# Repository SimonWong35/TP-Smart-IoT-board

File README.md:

# TP-Smart-IoT-board

## Schematic

## Layout (71mm x 60mm)

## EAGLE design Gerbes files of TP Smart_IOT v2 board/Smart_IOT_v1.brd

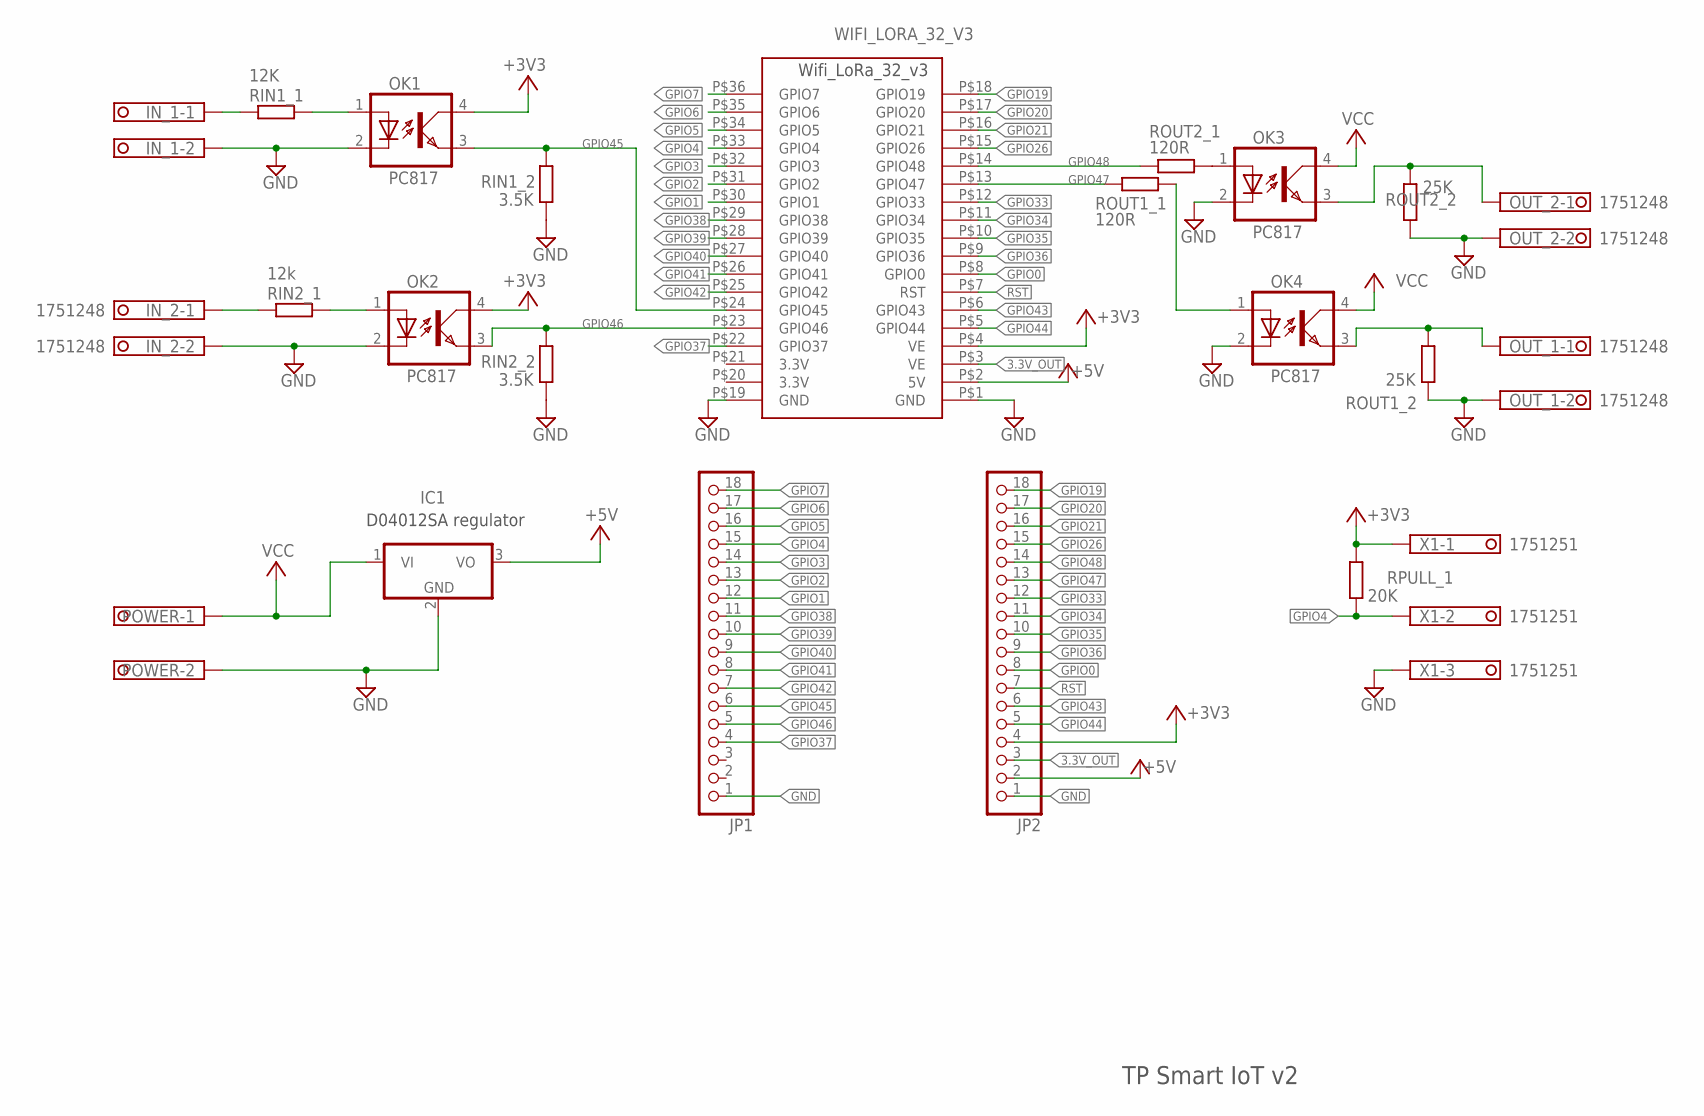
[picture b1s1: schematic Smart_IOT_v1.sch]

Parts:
IC1: 7805TV; TO220V
IN_1, IN_2: 1751248
JP1, JP2: PINHD-1X18; 1X18
OK1, OK2, OK3, OK4: PC817; DIL04
OUT_1, OUT_2: 1751248
POWER: 1751248
RIN1_1: 12K; M1206
RIN1_2, RIN2_2: 3.5K; M1206
RIN2_1: 12k; M1206
ROUT1_1, ROUT2_1: 120R; M1206
ROUT1_2, ROUT2_2: 25K; M1206
RPULL_1: 20K; M1206
WIFI_LORA_32_V3: WIFI_LORA_32_V3
X1: 1751251

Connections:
3.3V_OUT: JP2.3, WIFI_LORA_32_V3.P$3 (VE)
+3V3: JP2.4, OK1.4 (COL), OK2.4 (COL), RPULL_1.2, WIFI_LORA_32_V3.P$4 (VE), X1.1
+5V: IC1.3 (VO), JP2.2, WIFI_LORA_32_V3.P$2 (5V)
GND: IC1.2 (GND), IN_1.2, IN_2.2, JP1.1, JP2.1, OK1.2 (C), OK2.2 (C), OK3.2 (C), OK4.2 (C), OUT_1.2, OUT_2.2, POWER.2, RIN1_2.1, RIN2_2.1, ROUT1_2.1, ROUT2_2.2, WIFI_LORA_32_V3.P$1 (GND), WIFI_LORA_32_V3.P$19 (GND), X1.3
GPIO0: JP2.8, WIFI_LORA_32_V3.P$8 (GPIO0)
GPIO1: JP1.12, WIFI_LORA_32_V3.P$30 (GPIO1)
GPIO2: JP1.13, WIFI_LORA_32_V3.P$31 (GPIO2)
GPIO3: JP1.14, WIFI_LORA_32_V3.P$32 (GPIO3)
GPIO4: JP1.15, RPULL_1.1, WIFI_LORA_32_V3.P$33 (GPIO4), X1.2
GPIO5: JP1.16, WIFI_LORA_32_V3.P$34 (GPIO5)
GPIO6: JP1.17, WIFI_LORA_32_V3.P$35 (GPIO6)
GPIO7: JP1.18, WIFI_LORA_32_V3.P$36 (GPIO7)
GPIO19: JP2.18, WIFI_LORA_32_V3.P$18 (GPIO19)
GPIO20: JP2.17, WIFI_LORA_32_V3.P$17 (GPIO20)
GPIO21: JP2.16, WIFI_LORA_32_V3.P$16 (GPIO21)
GPIO26: JP2.15, WIFI_LORA_32_V3.P$15 (GPIO26)
GPIO33: JP2.12, WIFI_LORA_32_V3.P$12 (GPIO33)
GPIO34: JP2.11, WIFI_LORA_32_V3.P$11 (GPIO34)
GPIO35: JP2.10, WIFI_LORA_32_V3.P$10 (GPIO35)
GPIO36: JP2.9, WIFI_LORA_32_V3.P$9 (GPIO36)
GPIO37: JP1.4, WIFI_LORA_32_V3.P$22 (GPIO37)
GPIO38: JP1.11, WIFI_LORA_32_V3.P$29 (GPIO38)
GPIO39: JP1.10, WIFI_LORA_32_V3.P$28 (GPIO39)
GPIO40: JP1.9, WIFI_LORA_32_V3.P$27 (GPIO40)
GPIO41: JP1.8, WIFI_LORA_32_V3.P$26 (GPIO41)
GPIO42: JP1.7, WIFI_LORA_32_V3.P$25 (GPIO42)
GPIO43: JP2.6, WIFI_LORA_32_V3.P$6 (GPIO43)
GPIO44: JP2.5, WIFI_LORA_32_V3.P$5 (GPIO44)
GPIO45: JP1.6, OK1.3 (EMIT), RIN1_2.2, WIFI_LORA_32_V3.P$24 (GPIO45)
GPIO46: JP1.5, OK2.3 (EMIT), RIN2_2.2, WIFI_LORA_32_V3.P$23 (GPIO46)
GPIO47: JP2.13, ROUT1_1.1, WIFI_LORA_32_V3.P$13 (GPIO47)
GPIO48: JP2.14, ROUT2_1.1, WIFI_LORA_32_V3.P$14 (GPIO48)
unnamed: OK3.3 (EMIT), OUT_2.1, ROUT2_2.1
unnamed: IN_1.1, RIN1_1.1
unnamed: OK1.1 (A), RIN1_1.2
unnamed: IN_2.1, RIN2_1.1
unnamed: OK2.1 (A), RIN2_1.2
unnamed: OK3.1 (A), ROUT2_1.2
unnamed: OK4.1 (A), ROUT1_1.2
unnamed: OK4.3 (EMIT), OUT_1.1, ROUT1_2.2
RST: JP2.7, WIFI_LORA_32_V3.P$7 (RST)
VCC: IC1.1 (VI), OK3.4 (COL), OK4.4 (COL), POWER.1

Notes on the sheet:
D04012SA regulator
TP Smart IoT v2

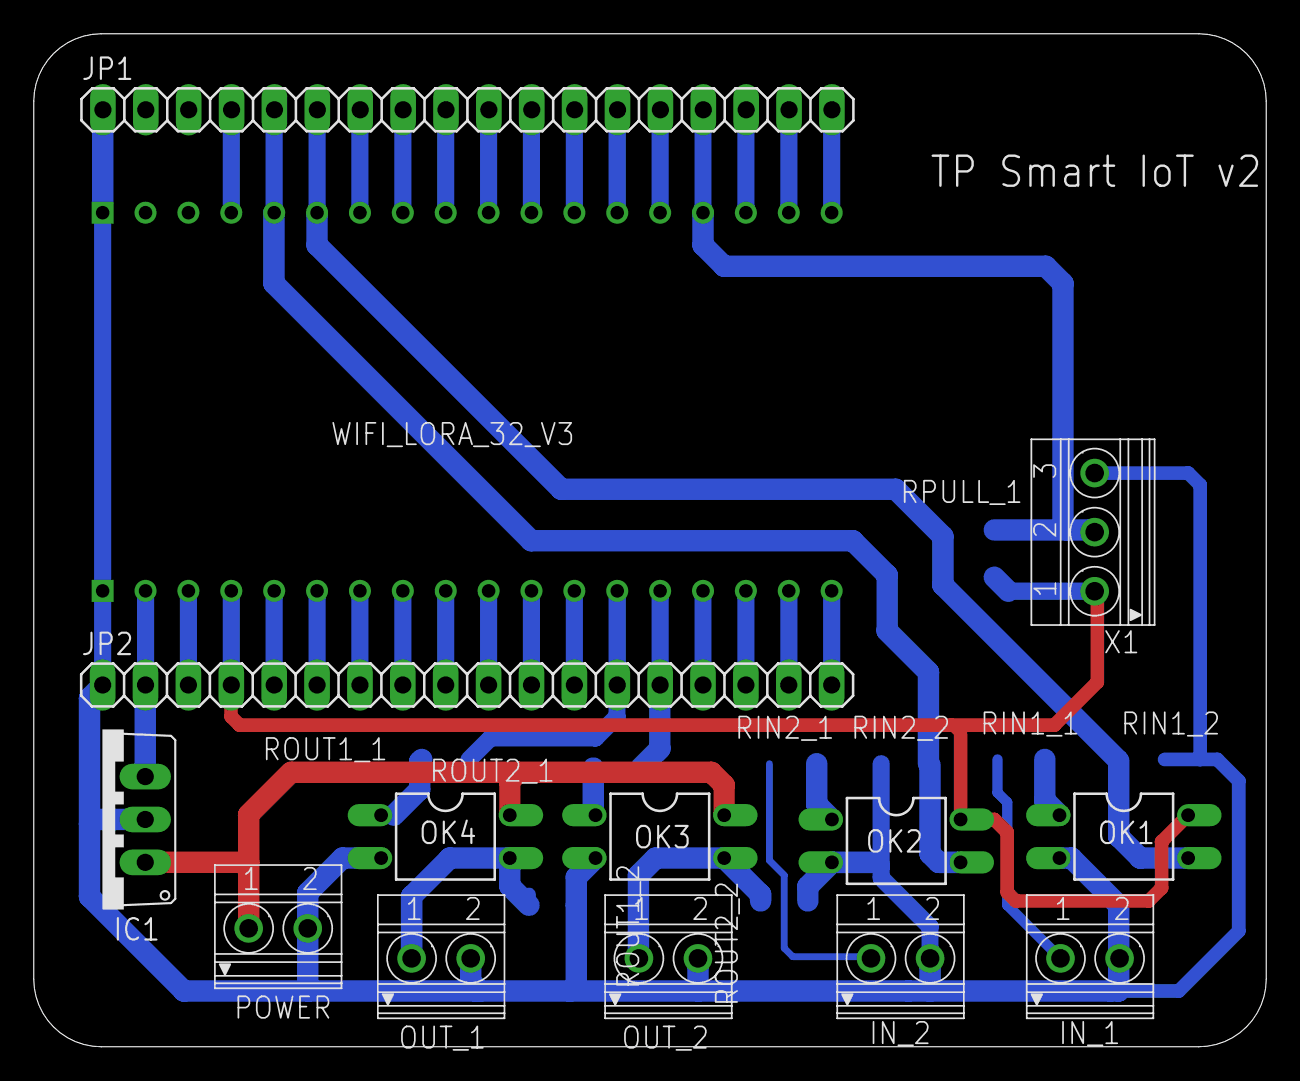
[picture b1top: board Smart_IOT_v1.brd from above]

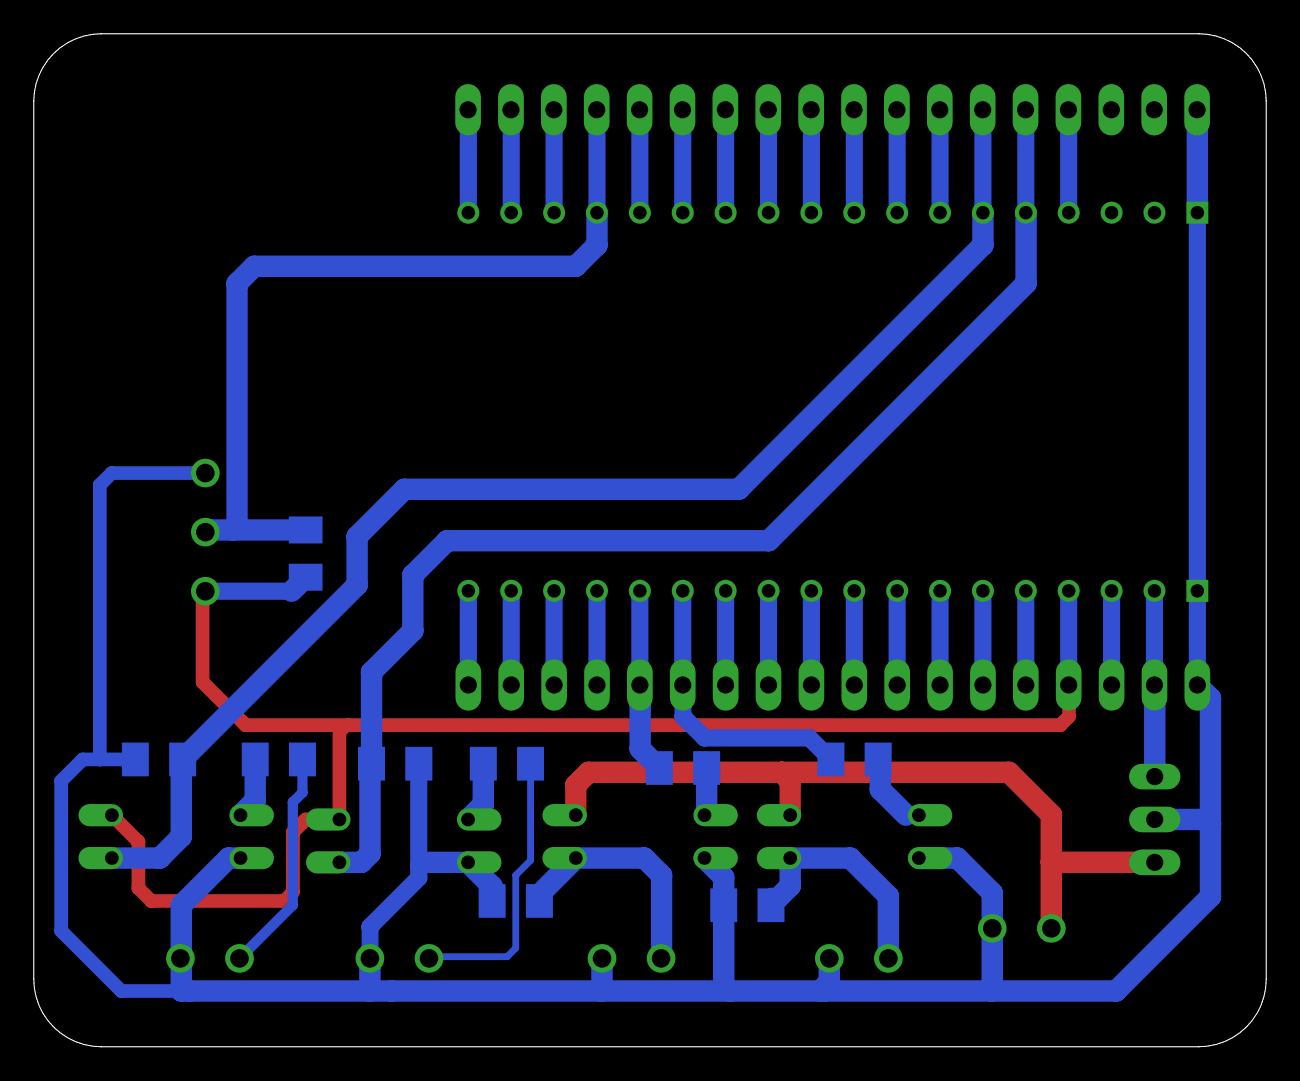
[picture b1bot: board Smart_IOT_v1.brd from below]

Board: 2 copper layers, 73.0 x 60.0 mm, 23 parts (9 on the bottom side), 42 nets.
